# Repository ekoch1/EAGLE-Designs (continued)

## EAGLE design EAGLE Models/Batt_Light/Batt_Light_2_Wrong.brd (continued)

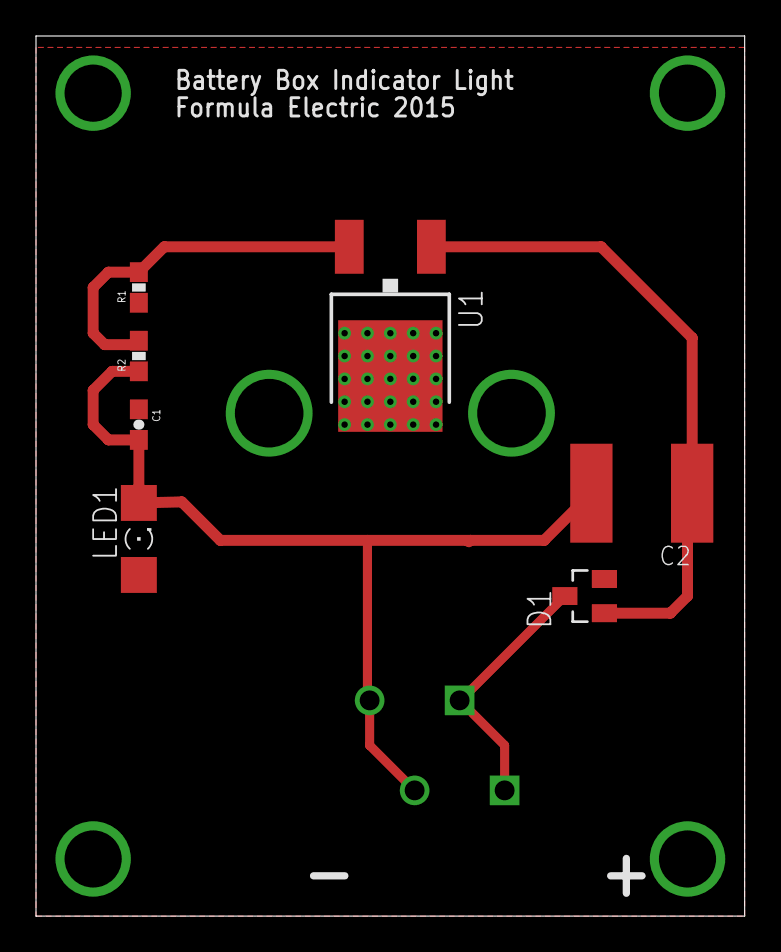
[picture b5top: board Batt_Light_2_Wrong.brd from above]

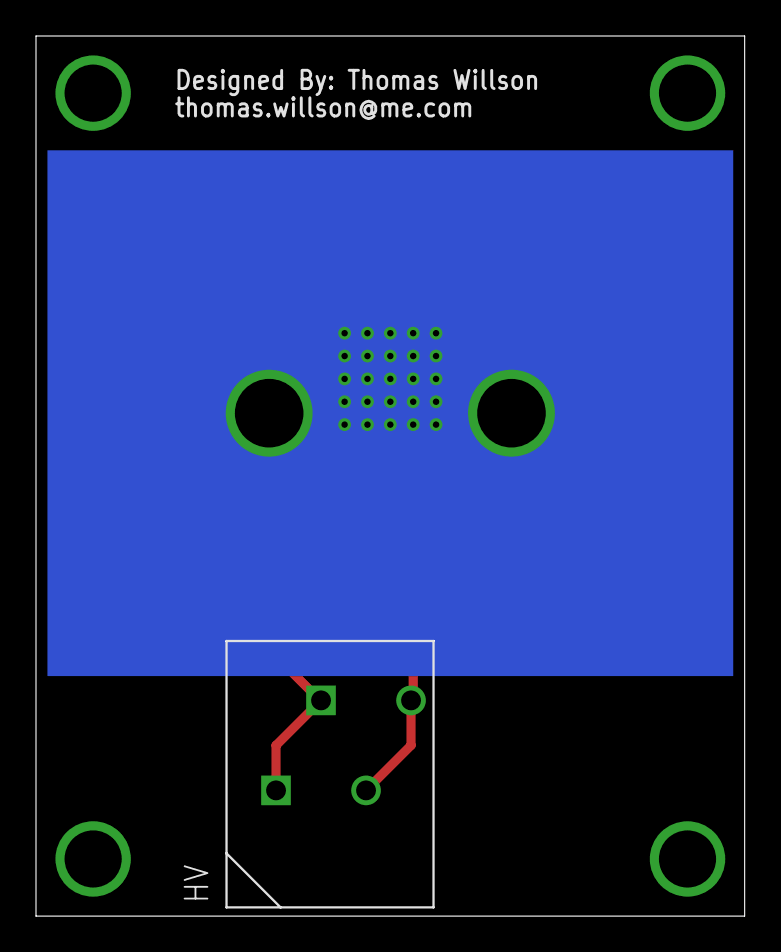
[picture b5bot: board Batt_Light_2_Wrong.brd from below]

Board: 2 copper layers, 39.4 x 48.9 mm, 9 parts (2 on the bottom side), 5 nets.
